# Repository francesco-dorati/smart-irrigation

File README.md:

# 🌿 Autonomous Plant Watering System

## Overview

This project aims to develop a **smart** and **autonomous** system for **watering indoor or outdoor plants**.  
The system is designed to **monitor soil moisture levels** and **automatically water** each plant when needed, making plant care effortless and reliable.

## 🌱 The Product

This system is designed to **take care of each plant separately** and **autonomously**.  
It provides **individualized watering** for each plant, ensuring they get exactly what they need—no more, no less.  
Perfect for balconies, gardens, or indoor setups.

1. **⚙️ Main Unit**  
   The central hub of the watering system, consisting of the **controller** and **water tank**.
   - 🪴 **Expandable** with up to **8 plants**  
   - 🔋 **Self-Sufficient** thanks to a **3500mAh battery**  
   - ☀️ **Solar Power** for complete autonomy

2. **🌿 Plant Unit**  
   A compact module attached to each plant, designed for **individual care**.
   - 📟 Composed of a **microcontroller**, **humidity sensor** and a **water pump**
   - 🔌 Connects to the Main Unit via an **Ethernet cable** and **water pipe**
   - 📏 Can be placed **up to 5 meters away** from the Main Unit

## 🚧 Project Status

- [x] Define system concept and design
- [x] Electrical scheme
- [x] Basic prototype
- [ ] Complete prototype with 1 plant
- [ ] Complete prototype with multiple plants
- [ ] Final enclosure design

## 📚 Resources
- ⚙️ Technical Details — [[here](docs/specifications.md)]
- 🧰  Components List — [[here](docs/components.md)]
- ⚡  Electrical Schemes — [[Main Unit](hardware/schematics/main_scheme.png) | [Plant Unit](hardware/schematics/plant_scheme.png)]
    
## 🤝 Contributing

Contributions, feedback, and suggestions are welcome!  
If you'd like to collaborate, please contact me via email:

**📧 fd.francescodorati@gmail.com**

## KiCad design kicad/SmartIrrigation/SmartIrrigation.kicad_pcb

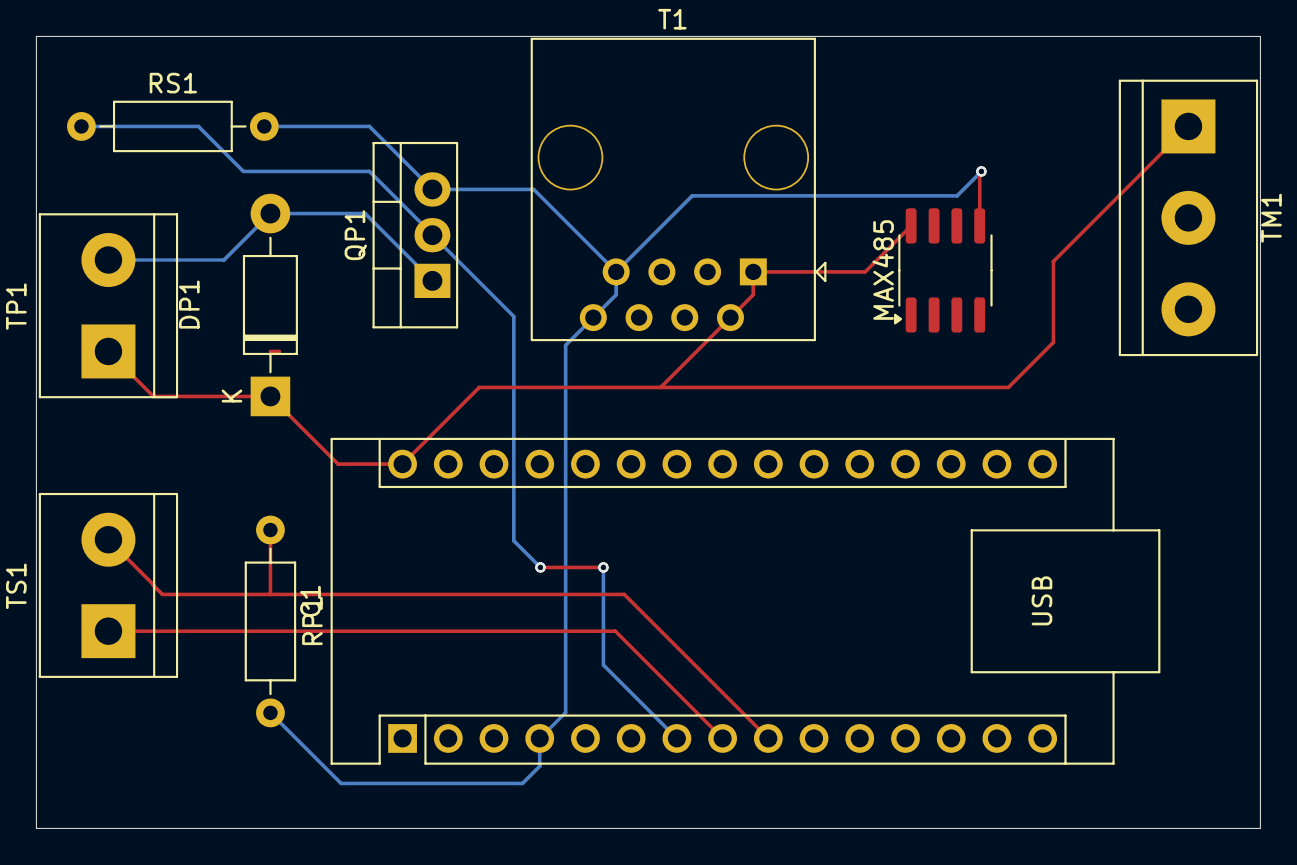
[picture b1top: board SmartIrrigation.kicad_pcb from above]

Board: 2 copper layers, 68.0 x 44.0 mm, 10 parts (0 on the bottom side), 12 nets.

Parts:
C1: Arduino Nano 5V; Arduino_Nano
DP1: 1N4007; D_DO-41_SOD81_P10.16mm_Horizontal
MAX485: Connection Module; SOIC-8_3.9x4.9mm_P1.27mm
QP1: IRLZ44N; TO-220-3_Vertical
RP1: 10k; R_Axial_DIN0207_L6.3mm_D2.5mm_P10.16mm_Horizontal
RS1: 10k; R_Axial_DIN0207_L6.3mm_D2.5mm_P10.16mm_Horizontal
T1: RJ45 Connector; RJ45_OST_PJ012-8P8CX_Vertical
TM1: Moisture Sensor; TerminalBlock_bornier-3_P5.08mm
TP1: Pump Termial; TerminalBlock_bornier-2_P5.08mm
TS1: Saucer Terminal; TerminalBlock_bornier-2_P5.08mm

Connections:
+5V: C1.30 (VIN), DP1.1 (K), MAX485.8 (VCC), T1.1, T1.2, TM1.1, TP1.1
GND: C1.4 (GND), MAX485.5 (GND), QP1.3 (S), RP1.2, RS1.2, T1.7, T1.8, TM1.3
unnamed: C1.19 (A0), TM1.2
unnamed: C1.6 (D3), MAX485.2 (~RE), MAX485.3 (DE)
unnamed: C1.7 (D4), QP1.2 (D), RS1.1
unnamed: C1.8 (D5), TS1.1
unnamed: C1.9 (D6), RP1.1, TS1.2
unnamed: C1.13 (D10), MAX485.1 (RO)
unnamed: C1.14 (D11), MAX485.4 (DI)
unnamed: DP1.2 (A), QP1.1 (G), TP1.2
unnamed: MAX485.6 (A), T1.3
unnamed: MAX485.7 (B), T1.4

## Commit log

2025-06-29 created folders
2025-06-29 added .gitignore
2025-06-29 changed schema
2025-06-29 plant client schema almost complete
2025-06-29 base schematics added
2025-06-30 modified base schematics
2025-07-05 modified schematics
2025-07-17 created basic prototype
2025-07-17 maincontroller demo
2025-07-18 sviluppate funzionalità demo
2025-07-18 saved schematics & formatted
2025-07-18 restructured codebase
2025-07-18 updated .gitignore
2025-07-18 undate .gitignore
2025-07-19 created upload scripts
2025-07-20 Refactor LED blink method and implement RTC and RS485 communication classes
2025-07-21 Add SaucerSensor class and electrical scheme for plant unit
    - Implemented SaucerSensor class with methods to initialize and check if the saucer is full.
    - Added initial electrical scheme for the plant unit in KiCad.
2025-07-21 Modifica il tipo di ID da String a int in diverse classi e aggiorna i metodi di ricezione e trasmissione per riflettere il cambiamento
2025-07-21 fix bugs
2025-07-23 Add SDCard class for managing plant data logging and loading
    - Created SDCard.cpp and SDCard.h files.
    - Implemented methods for loading plant data and logging various plant statuses.
    - Prepared the class for future expansion with additional functionalities.
2025-07-24 added schematics images
2025-07-27 change spec: implementing evapotranspiration (ET)
2025-07-27 rename and restore old spec
2025-08-05 new schemes
2025-08-11 Refactor Controller class and enhance WiFiManager functionality; add sleep feature and improve power management
2025-08-11 updated schematics
2025-08-25 Add SD card support
